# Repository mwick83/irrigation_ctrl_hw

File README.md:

# Irrigation Controller (hardware repo)

This is the hardware repository for the Irrigation Controller project. The repository holding the software of the project contains the documentation. Please refer to [https://github.com/mwick83/irrigation_ctrl](https://github.com/mwick83/irrigation_ctrl).

## License

Copyright (c) 2017-2018 Manuel Wick

Licensed under the BSD 3-clause "New" or "Revised" License.
See LICENSE.md file or [http://www.opensource.org/licenses/BSD-3-Clause](http://www.opensource.org/licenses/BSD-3-Clause) for details.

## Archived footprints

Please note that most of the footprints in directories "archived_footprints.pretty" are derived from the KiCAD distribution. They are licensed under their own associated license. These footprints are only provided for convenience and archiving purposes.

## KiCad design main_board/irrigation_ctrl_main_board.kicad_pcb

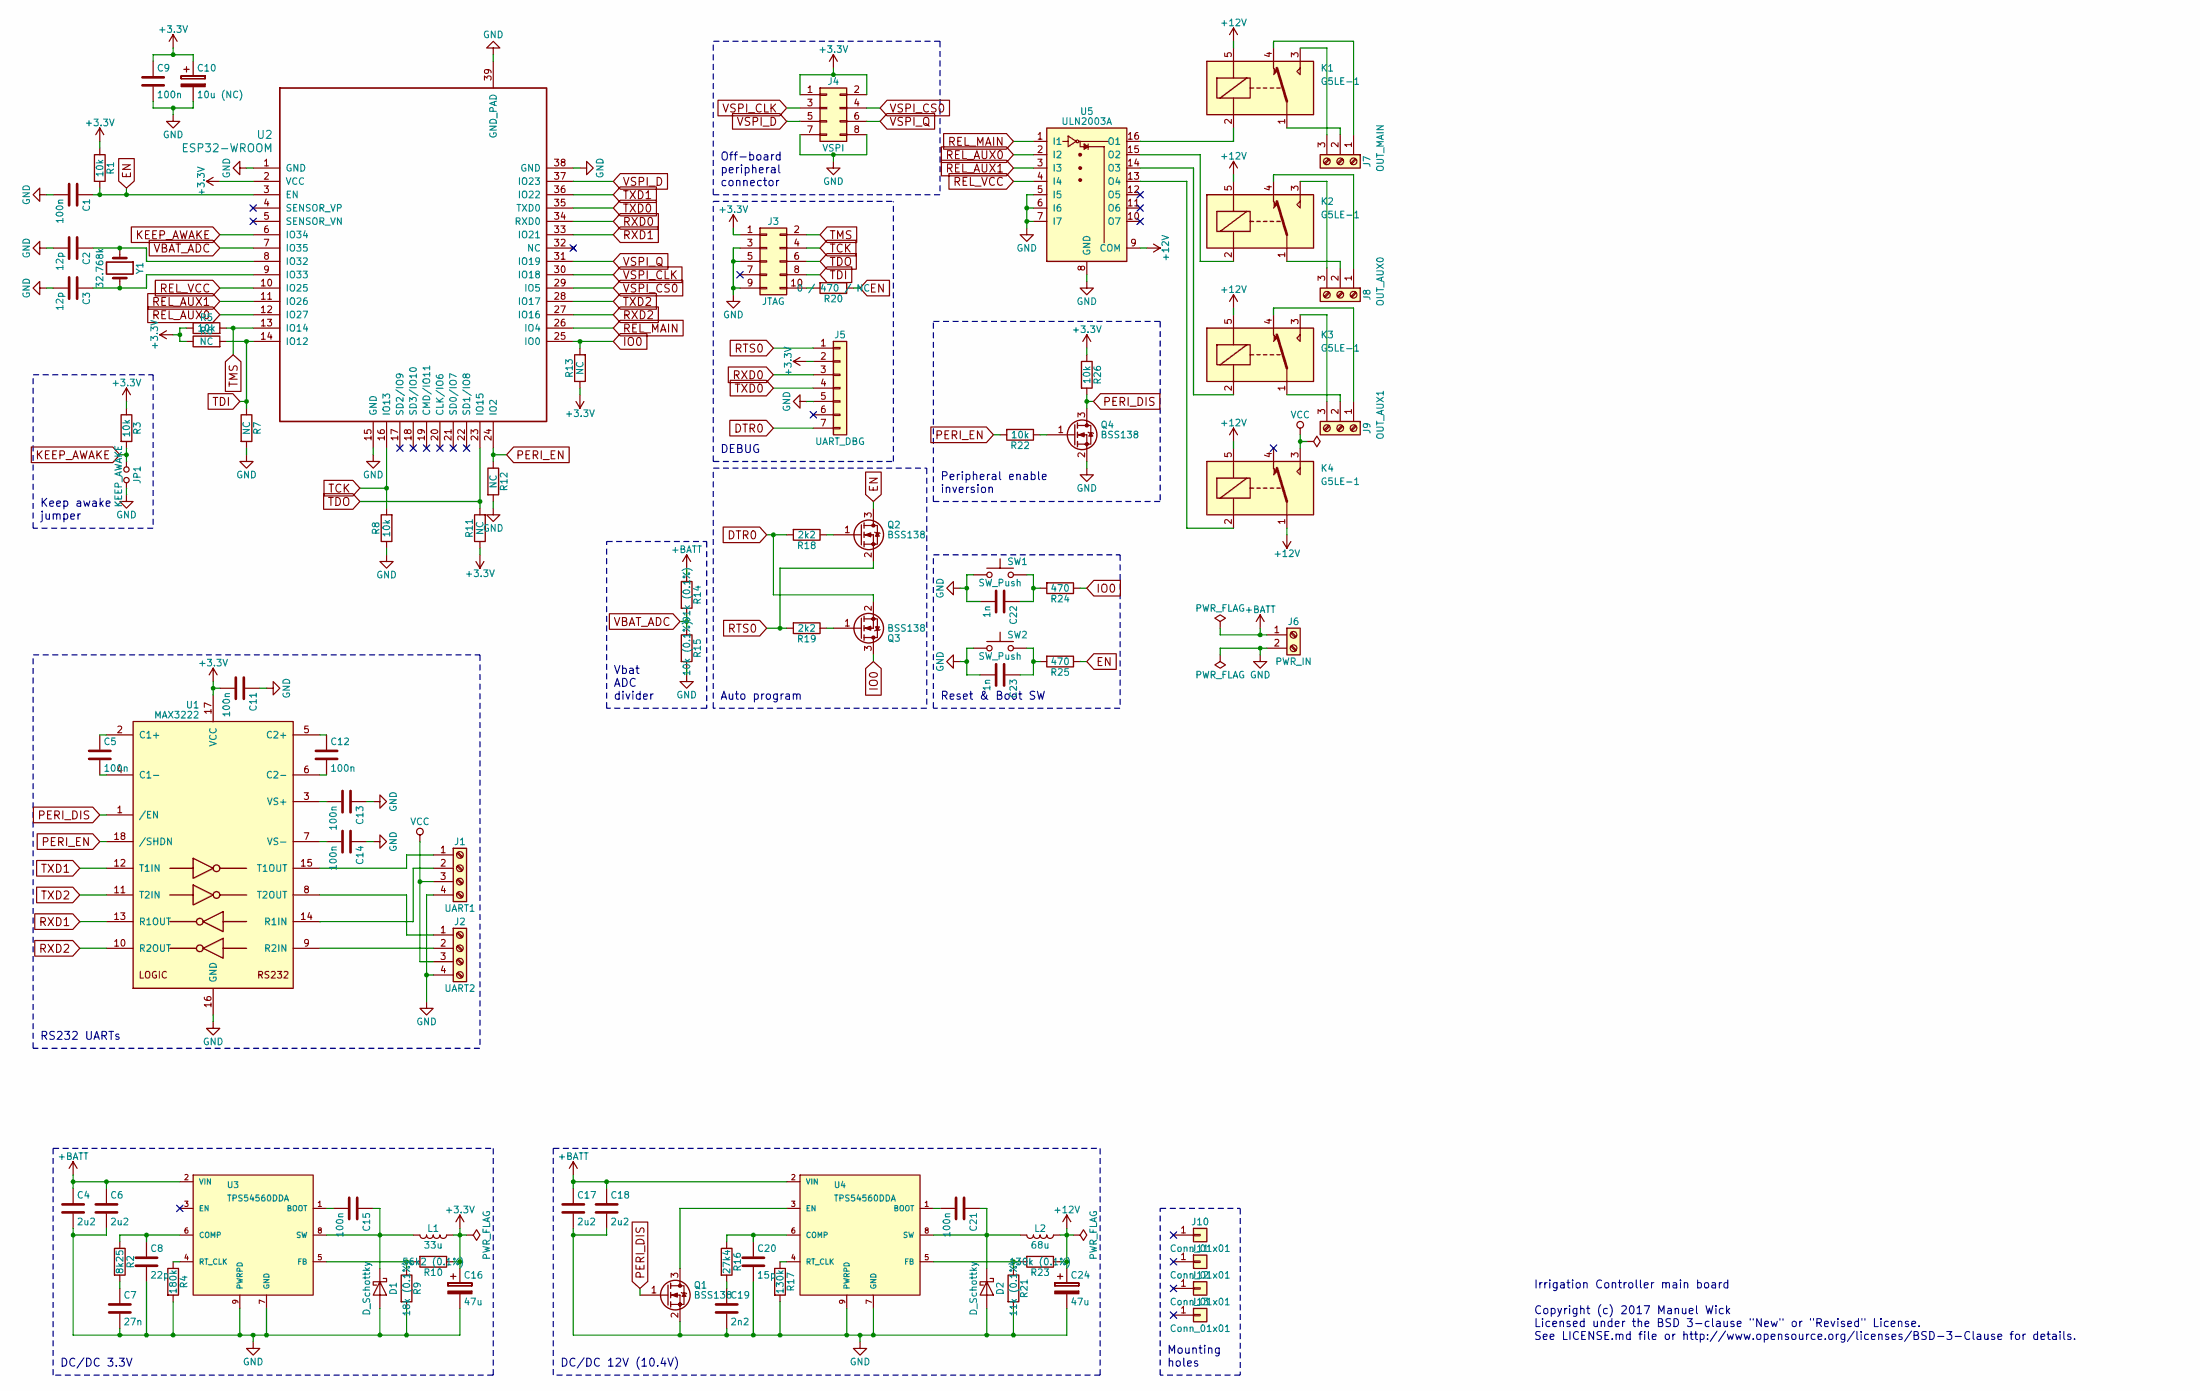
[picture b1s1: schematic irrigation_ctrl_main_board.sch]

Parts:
C1, C5, C9, C11, C12, C13, C14, C15, C21: 100n; C_0805_HandSoldering
C2, C3: 12p; C_0805_HandSoldering
C4, C6, C17, C18: 2u2; C_1206_HandSoldering
C7: 27n; C_0805_HandSoldering
C8: 22p; C_0805_HandSoldering
C10: 10u (NC); C_1206_HandSoldering
C16, C24: 47u; CP_Elec_8x6.7
C19: 2n2; C_0805_HandSoldering
C20: 15p; C_0805_HandSoldering
C22, C23: 1n; C_0805_HandSoldering
D1, D2: D_Schottky; D_SMC_Handsoldering
J1: UART1; AKL230-04
J2: UART2; AKL230-04
J3: JTAG; IDC_Header_Straight_10pins_005
J4: VSPI; Pin_Header_Straight_2x04_Pitch2.54mm
J5: UART_DBG; Pin_Header_Straight_1x07_Pitch2.54mm
J6: PWR_IN; AKL230-02
J7: OUT_MAIN; AKL230-03
J8: OUT_AUX0; AKL230-03
J9: OUT_AUX1; AKL230-03
J10, J11, J12, J13: Conn_01x01; MountingHole_3.2mm_M3
JP1: KEEP_AWAKE; Pin_Header_Straight_1x02_Pitch2.54mm
K1, K2, K3, K4: G5LE-1; Relay_SPDT_OMRON-G5LE-1
L1: 33u; L_7.3x7.3_H4.5
L2: 68u; L_7.3x7.3_H4.5
Q1, Q2, Q3, Q4: BSS138; SOT-23
R1, R3, R5, R8, R22, R26: 10k; R_0805_HandSoldering
R2: 8k25; R_0805_HandSoldering
R4: 180k; R_0805_HandSoldering
R6, R7, R11, R12, R13: NC; R_0805_HandSoldering
R9: 18k (0.1%); R_0805_HandSoldering
R10: 56k2 (0.1%); R_0805_HandSoldering
R14: 91k (0.1%); R_0805_HandSoldering
R15: 10k (0.1%); R_0805_HandSoldering
R16: 27k4; R_0805_HandSoldering
R17: 130k; R_0805_HandSoldering
R18, R19: 2k2; R_0805_HandSoldering
R20: 0 / 470 / NC; R_0805_HandSoldering
R21: 11k (0.1%); R_0805_HandSoldering
R23: 130k (0.1%); R_0805_HandSoldering
R24, R25: 470; R_0805_HandSoldering
SW1, SW2: SW_Push; SW_SPST_REICHELT_SMD
U1: MAX3222; SOIC-18W_7.5x11.6mm_Pitch1.27mm
U2: ESP32-WROOM
U3, U4: TPS54560DDA; TI_SO-PowerPAD-8
U5: ULN2003A; SOIC-16_3.9x9.9mm_Pitch1.27mm
Y1: 32.768k; Crystal_DS26_d2.0mm_l6.0mm_Horizontal

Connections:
+3V3: C9.1, C10.1, C11.2, C16.1, J3.1, J4.1, J4.2, J5.2, L1.1, R1.1, R3.1, R5.1, R6.1, R10.1, R11.1, R13.1, R26.1, U1.17 (VCC), U2.2 (VCC)
+12V: C24.1, K1.5, K2.5, K3.5, K4.1, K4.5, L2.1, R23.1, U5.9 (COM)
+BATT: C4.1, C6.1, C17.1, C18.1, J6.1, R14.1, U3.2 (VIN), U4.2 (VIN)
DTR0: J5.7, Q3.2 (S), R18.2
EN: C1.1, Q2.3 (D), R1.2, R20.1, R25.1, U2.3 (EN)
GND: C1.2, C2.2, C3.2, C4.2, C6.2, C7.2, C8.2, C9.2, C10.2, C11.1, C13.1, C14.1, C16.2, C17.2, C18.2, C19.2, C20.2, C22.2, C23.2, C24.2, D1.2 (A), D2.2 (A), J1.4, J2.4, J3.3, J3.5, J3.9, J4.7, J4.8, J5.5, J6.2, JP1.2, Q1.2 (S), Q4.2 (S), R4.2, R7.2, R8.1, R9.2, R12.2, R15.2, R17.2, R21.2, SW1.1, SW2.1, U1.16 (GND), U2.1 (GND), U2.15 (GND), U2.38 (GND), U2.39 (GND_PAD), U3.7 (GND), U3.9 (PWRPD), U4.7 (GND), U4.9 (PWRPD), U5.5 (I5), U5.6 (I6), U5.7 (I7), U5.8 (GND)
IO0: Q3.3 (D), R13.2, R24.1, U2.25 (IO0)
KEEP_AWAKE: JP1.1, R3.2, U2.6 (IO34)
unnamed: C2.1, U2.8 (IO32), Y1.1
unnamed: C3.1, U2.9 (IO33), Y1.2
unnamed: C5.1, U1.2 (C1+)
unnamed: C5.2, U1.4 (C1-)
unnamed: C7.1, R2.2
unnamed: C8.1, R2.1, U3.6 (COMP)
unnamed: C12.1, U1.5 (C2+)
unnamed: C12.2, U1.6 (C2-)
unnamed: C13.2, U1.3 (VS+)
unnamed: C14.2, U1.7 (VS-)
unnamed: C15.1, D1.1 (K), L1.2, U3.8 (SW)
unnamed: C15.2, U3.1 (BOOT)
unnamed: C19.1, R16.2
unnamed: C20.1, R16.1, U4.6 (COMP)
unnamed: C21.1, D2.1 (K), L2.2, U4.8 (SW)
unnamed: C21.2, U4.1 (BOOT)
unnamed: C22.1, R24.2, SW1.2
unnamed: C23.1, R25.2, SW2.2
unnamed: J1.1, U1.15 (T1OUT)
unnamed: J1.2, U1.14 (R1IN)
unnamed: J2.1, U1.8 (T2OUT)
unnamed: J2.2, U1.9 (R2IN)
unnamed: J3.10, R20.2
unnamed: J7.1, K1.4
unnamed: J7.2, K1.1
unnamed: J7.3, K1.3
unnamed: J8.1, K2.4
unnamed: J8.2, K2.1
unnamed: J8.3, K2.3
unnamed: J9.1, K3.4
unnamed: J9.2, K3.1
unnamed: J9.3, K3.3
unnamed: K1.2, U5.16 (O1)
unnamed: K2.2, U5.15 (O2)
unnamed: K3.2, U5.14 (O3)
unnamed: K4.2, U5.13 (O4)
unnamed: Q1.3 (D), U4.3 (EN)
unnamed: Q2.1 (G), R18.1
unnamed: Q3.1 (G), R19.1
unnamed: Q4.1 (G), R22.1
unnamed: R4.1, U3.4 (RT_CLK)
unnamed: R9.1, R10.2, U3.5 (FB)
unnamed: R17.1, U4.4 (RT_CLK)
unnamed: R21.1, R23.2, U4.5 (FB)
PERI_DIS: Q1.1 (G), Q4.3 (D), R26.2, U1.1 (/EN)
PERI_EN: R12.1, R22.2, U1.18 (/SHDN), U2.24 (IO2)
REL_AUX0: U2.12 (IO27), U5.2 (I2)
REL_AUX1: U2.11 (IO26), U5.3 (I3)
REL_MAIN: U2.26 (IO4), U5.1 (I1)
REL_VCC: U2.10 (IO25), U5.4 (I4)
RTS0: J5.1, Q2.2 (S), R19.2
RXD0: J5.3, U2.34 (RXD0)
RXD1: U1.13 (R1OUT), U2.33 (IO21)
RXD2: U1.10 (R2OUT), U2.27 (IO16)
TCK: J3.4, R8.2, U2.16 (IO13)
TDI: J3.8, R6.2, R7.1, U2.14 (IO12)
TDO: J3.6, R11.2, U2.23 (IO15)
TMS: J3.2, R5.2, U2.13 (IO14)
TXD0: J5.4, U2.35 (TXD0)
TXD1: U1.12 (T1IN), U2.36 (IO22)
TXD2: U1.11 (T2IN), U2.28 (IO17)
VBAT_ADC: R14.2, R15.1, U2.7 (IO35)
VCC: J1.3, J2.3, K4.3
VSPI_CLK: J4.3, U2.30 (IO18)
VSPI_CS0: J4.4, U2.29 (IO5)
VSPI_D: J4.5, U2.37 (IO23)
VSPI_Q: J4.6, U2.31 (IO19)

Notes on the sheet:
Auto program
Reset & Boot SW
Keep awake jumper
DEBUG
RS232 UARTs
Vbat ADC divider
Off-board peripheral connector
DC/DC 3.3V
DC/DC 12V (10.4V)
Peripheral enable inversion
Irrigation Controller main board Copyright (c) 2017 Manuel Wick Licensed under the BSD 3-clause "New" or "Revised" License. See LICENSE.md file or http://www.opensource.org/licenses/BSD-3-Clause for details.
Mounting holes

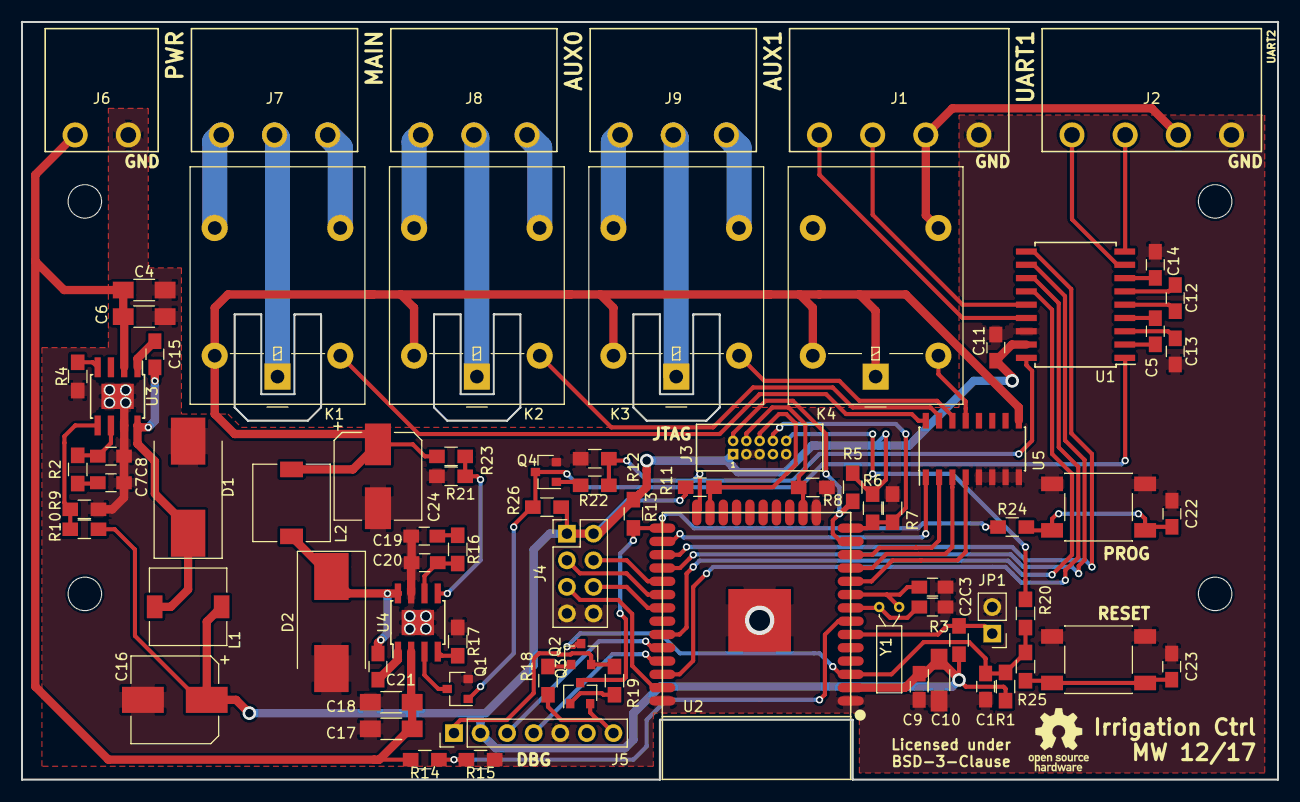
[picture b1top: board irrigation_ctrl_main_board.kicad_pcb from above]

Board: 2 copper layers, 120.0 x 72.4 mm, 84 parts (0 on the bottom side), 75 nets.

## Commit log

2017-10-31 Add webench DCDC exproted files
2017-10-31 Initial gitignore file
2017-10-31 Add completed main board
2017-11-14 Update of manufactured state
    Moved notes of the schematic to the correct part. Updated XML file,
    which has been missed on manufactured checkin.
2017-11-14 Updated AKL footprints
    Changed footprints to match diameter recommended by manufacturer.
2018-01-07 Removed temporary exported DCDC converter designs
2018-01-21 Preparations for publication
2018-01-24 Added exported schematics
